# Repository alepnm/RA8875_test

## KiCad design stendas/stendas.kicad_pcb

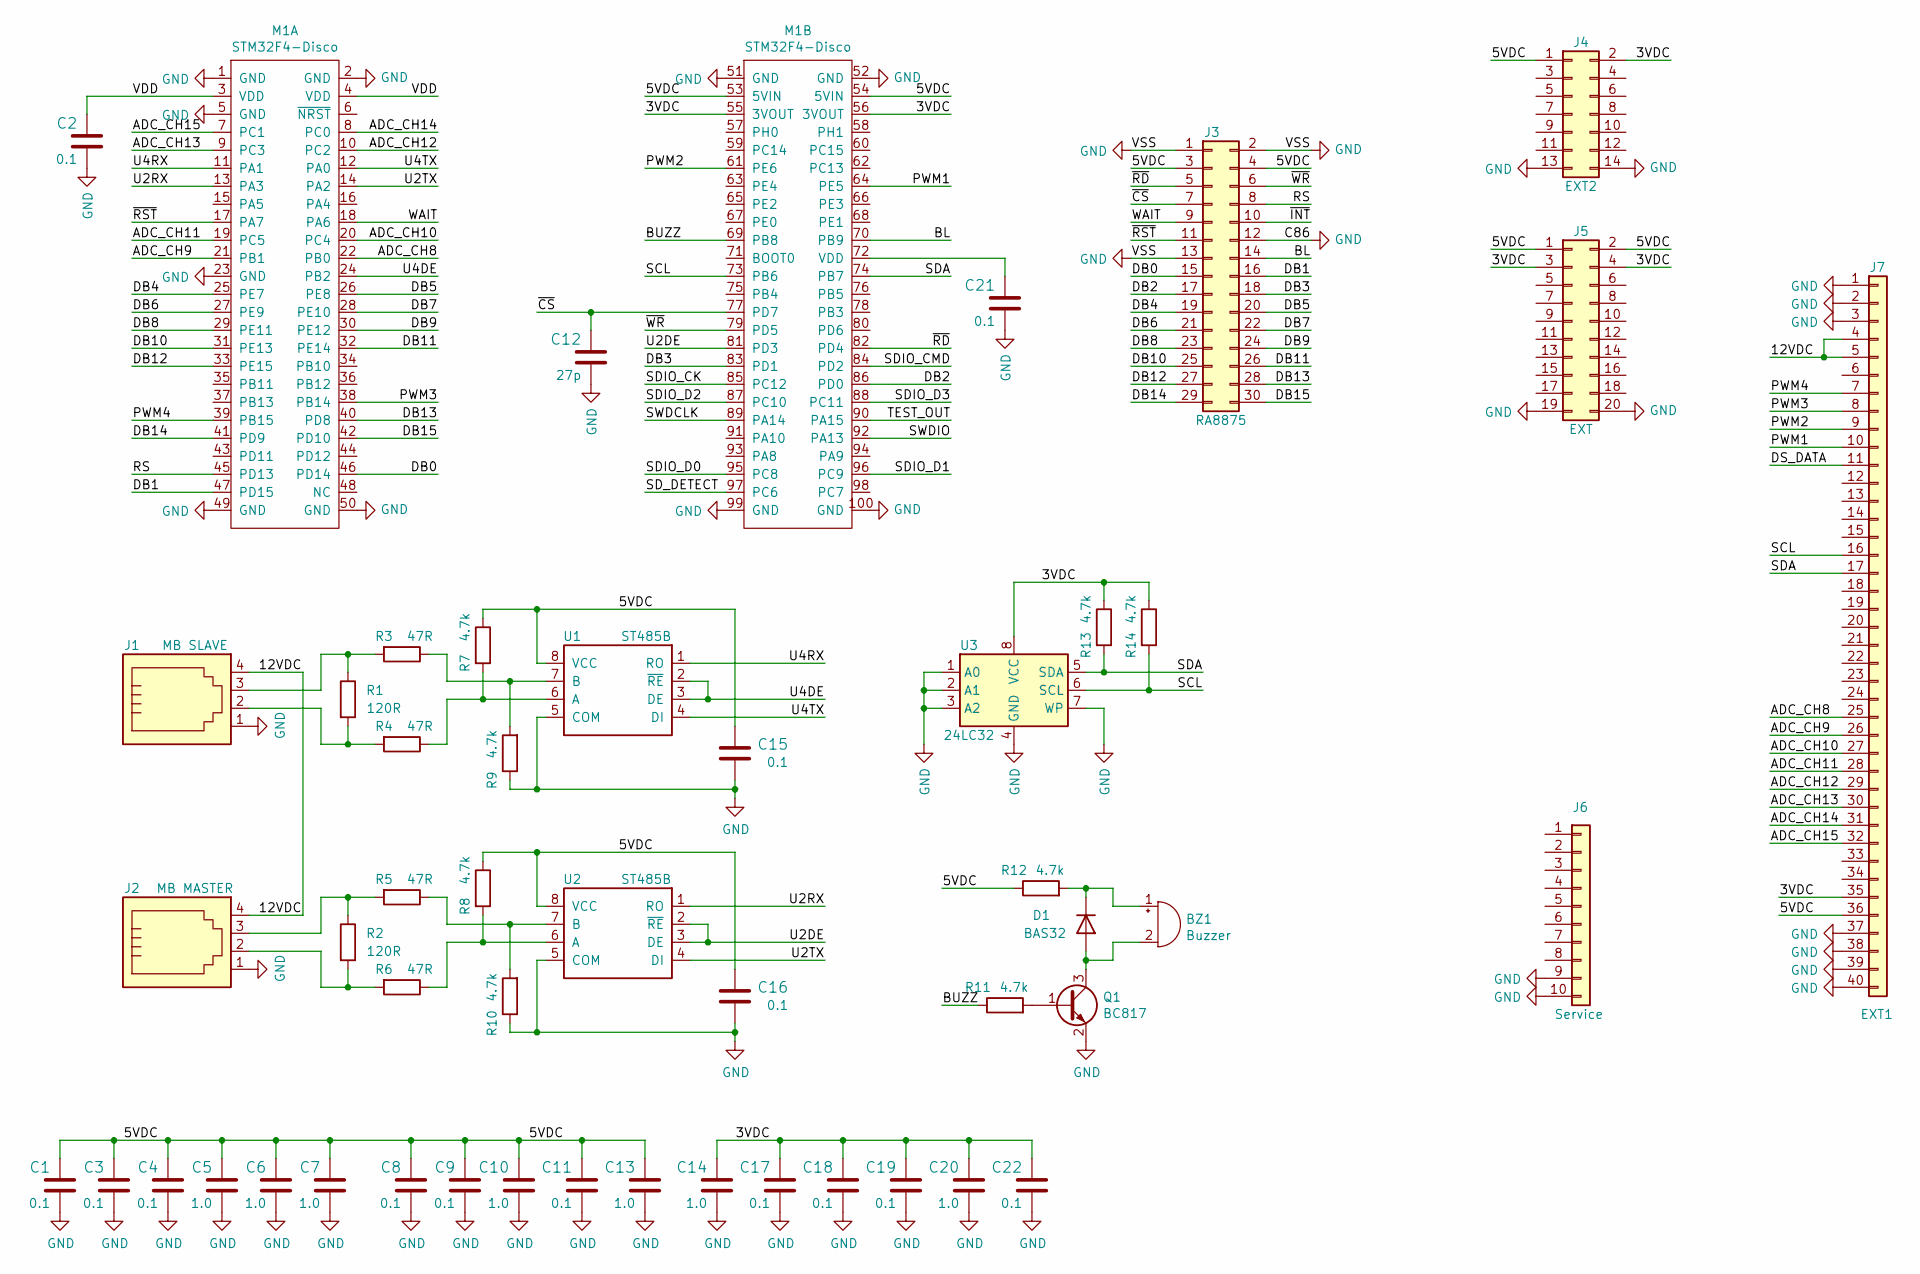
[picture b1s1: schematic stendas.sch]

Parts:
BZ1: Buzzer; MagneticBuzzer_Kobitone_254-EMB84Q-RO
C1, C2, C3, C4, C8, C9, C11, C15, C16, C17, C18, C19, C21, C22: 0.1; C_0805_2012Metric
C5, C6, C7, C10, C13, C14, C20: 1.0; C_1206_3216Metric
C12: 27p
D1: BAS32; D_MiniMELF
J1: MB SLAVE; RJ11_4P_Vertical_DIP
J2: MB MASTER; RJ11_4P_Vertical_DIP
J3: RA8875; PinHeader_2x15_P2.54mm_Vertical
J4: EXT2; IDC-Header_2x07_P2.54mm_Vertical
J5: EXT; IDC-Header_2x10_P2.54mm_Vertical
J6: Service; PinHeader_1x10_P2.54mm_Vertical
J7: EXT1; PinHeader_1x40_P2.54mm_Vertical
M1: STM32F4-Disco; STM32F4_Disco
Q1: BC817; SOT-23
R1, R2: 120R; R_1206_3216Metric
R3, R4, R5, R6: 47R; R_0805_2012Metric
R7, R8, R9, R10, R11, R12, R13, R14: 4.7k; R_0805_2012Metric
U1, U2: ST485B; SOIC-8_3.9x4.9mm_P1.27mm
U3: 24LC32; SOIC-8_3.9x4.9mm_P1.27mm

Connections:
/3VDC: C14.2, C17.2, C18.2, C19.2, C20.2, C22.2, J4.2, J5.3, J5.4, J7.35, M1.55 (3VOUT), M1.56 (3VOUT), R13.1, R14.1, U3.8 (VCC)
/5VDC: C1.2, C3.2, C4.2, C5.2, C6.2, C7.2, C8.2, C9.2, C10.2, C11.2, C13.2, C15.2, C16.2, J3.3, J3.4, J4.1, J5.1, J5.2, J7.36, M1.53 (5VIN), M1.54 (5VIN), R7.1, R8.1, R12.1, U1.8 (VCC), U2.8 (VCC); also elsewhere on the board
/12VDC: J1.4, J2.4, J7.4, J7.5
/ADC_CH8: J7.25, M1.22 (PB0)
/ADC_CH9: J7.26, M1.21 (PB1)
/ADC_CH10: J7.27, M1.20 (PC4)
/ADC_CH11: J7.28, M1.19 (PC5)
/ADC_CH12: J7.29, M1.10 (PC2)
/ADC_CH13: J7.30, M1.9 (PC3)
/ADC_CH14: J7.31, M1.8 (PC0)
/ADC_CH15: J7.32, M1.7 (PC1)
/BL: J3.14, M1.70 (PB9)
/BUZZ: M1.69 (PB8), R11.1; also elsewhere on the board
/DB0: J3.15, M1.46 (PD14)
/DB1: J3.16, M1.47 (PD15)
/DB2: J3.17, M1.86 (PD0)
/DB3: J3.18, M1.83 (PD1)
/DB4: J3.19, M1.25 (PE7)
/DB5: J3.20, M1.26 (PE8)
/DB6: J3.21, M1.27 (PE9)
/DB7: J3.22, M1.28 (PE10)
/DB8: J3.23, M1.29 (PE11)
/DB9: J3.24, M1.30 (PE12)
/DB10: J3.25, M1.31 (PE13)
/DB11: J3.26, M1.32 (PE14)
/DB12: J3.27, M1.33 (PE15)
/DB13: J3.28, M1.40 (PD8)
/DB14: J3.29, M1.41 (PD9)
/DB15: J3.30, M1.42 (PD10)
/DS_DATA: J7.11
/PWM1: J7.10, M1.64 (PE5)
/PWM2: J7.9, M1.61 (PE6)
/PWM3: J7.8, M1.38 (PB14)
/PWM4: J7.7, M1.39 (PB15)
/RS: J3.8, M1.45 (PD13)
/SCL: J7.16, M1.73 (PB6), R14.2, U3.6 (SCL)
/SDA: J7.17, M1.74 (PB7), R13.2, U3.5 (SDA)
/SDIO_CK: M1.85 (PC12)
/SDIO_CMD: M1.84 (PD2)
/SDIO_D0: M1.95 (PC8)
/SDIO_D1: M1.96 (PC9)
/SDIO_D2: M1.87 (PC10)
/SDIO_D3: M1.88 (PC11)
/SD_DETECT: M1.97 (PC6)
/SWDCLK: M1.89 (PA14)
/SWDIO: M1.92 (PA13)
/TEST_OUT: M1.90 (PA15)
/U2DE: M1.81 (PD3), U2.2 (~RE), U2.3 (DE)
/U2RX: M1.13 (PA3), U2.1 (RO)
/U2TX: M1.14 (PA2), U2.4 (DI)
/U4DE: M1.24 (PB2), U1.2 (~RE), U1.3 (DE); also elsewhere on the board
/U4RX: M1.11 (PA1), U1.1 (RO); also elsewhere on the board
/U4TX: M1.12 (PA0), U1.4 (DI); also elsewhere on the board
/VDD: C2.2, M1.3 (VDD), M1.4 (VDD)
/WAIT: J3.9, M1.18 (PA6)
/~CS: C12.2, J3.7, M1.77 (PD7)
/~INT: J3.10
/~RD: J3.5, M1.82 (PD4)
/~RST: J3.11, M1.17 (PA7)
/~WR: J3.6, M1.79 (PD5)
GND: C1.1, C2.1, C3.1, C4.1, C5.1, C6.1, C7.1, C8.1, C9.1, C10.1, C11.1, C12.1, C13.1, C14.1, C15.1, C16.1, C17.1, C18.1, C19.1, C20.1, C21.1, C22.1, J1.1, J2.1, J3.1, J3.2, J3.12, J3.13, J4.13, J4.14, J5.19, J5.20, J6.9, J6.10, J7.1, J7.2, J7.3, J7.37, J7.38, J7.39, J7.40, M1.1 (GND), M1.2 (GND), M1.5 (GND), M1.23 (GND), M1.49 (GND), M1.50 (GND), M1.51 (GND), M1.52 (GND), M1.99 (GND), M1.100 (GND), Q1.2 (E), R9.1, R10.1, U1.5 (COM), U2.5 (COM), U3.1 (A0), U3.2 (A1), U3.3 (A2), U3.4 (GND), U3.7 (WP)
unnamed: BZ1.1 (-), D1.1 (K), R12.2
unnamed: BZ1.2 (+), D1.2 (A), Q1.3 (C)
unnamed: C21.2, M1.72 (VDD)
unnamed: J1.2, R1.2, R4.2
unnamed: J1.3, R1.1, R3.2
unnamed: J2.2, R2.2, R6.2
unnamed: J2.3, R2.1, R5.2
unnamed: Q1.1 (B), R11.2
unnamed: R3.1, R9.2, U1.7 (B)
unnamed: R4.1, R7.2, U1.6 (A)
unnamed: R6.1, R8.2, U2.6 (A)
unnamed: R5.1, R10.2, U2.7 (B)

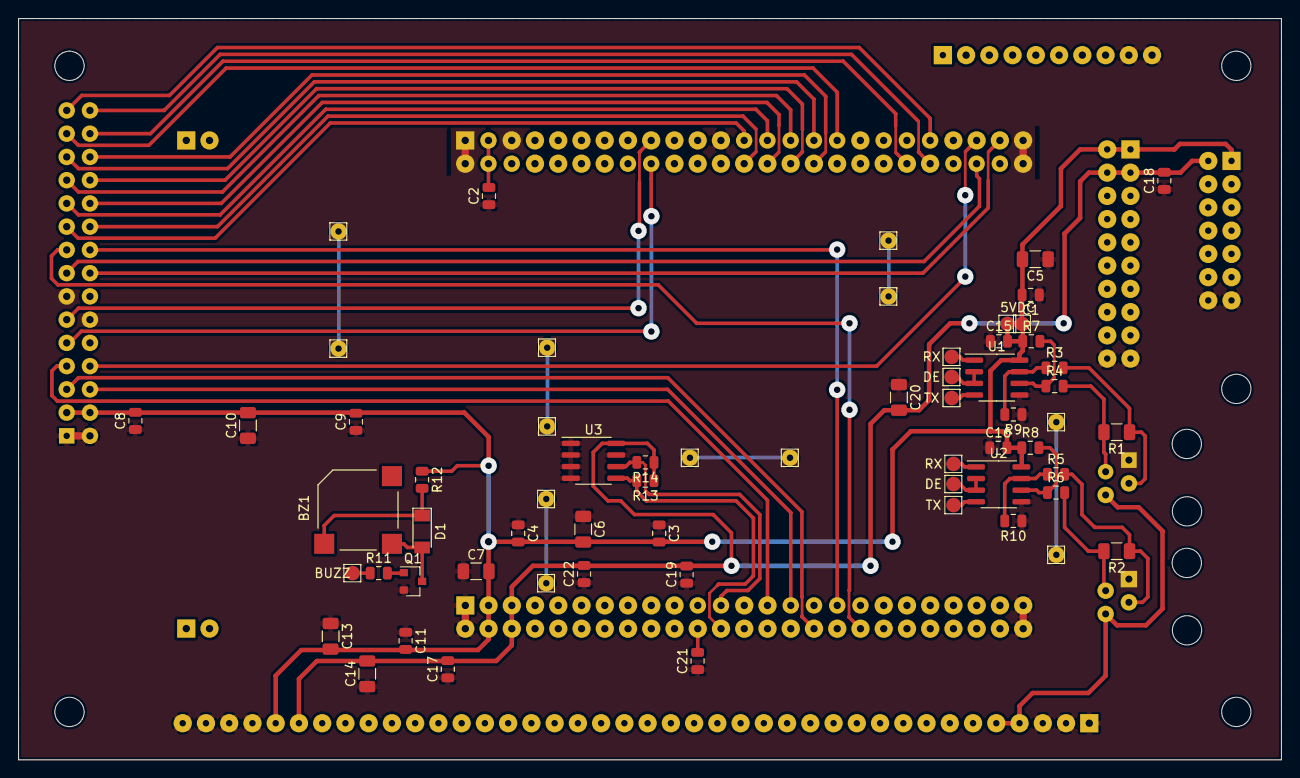
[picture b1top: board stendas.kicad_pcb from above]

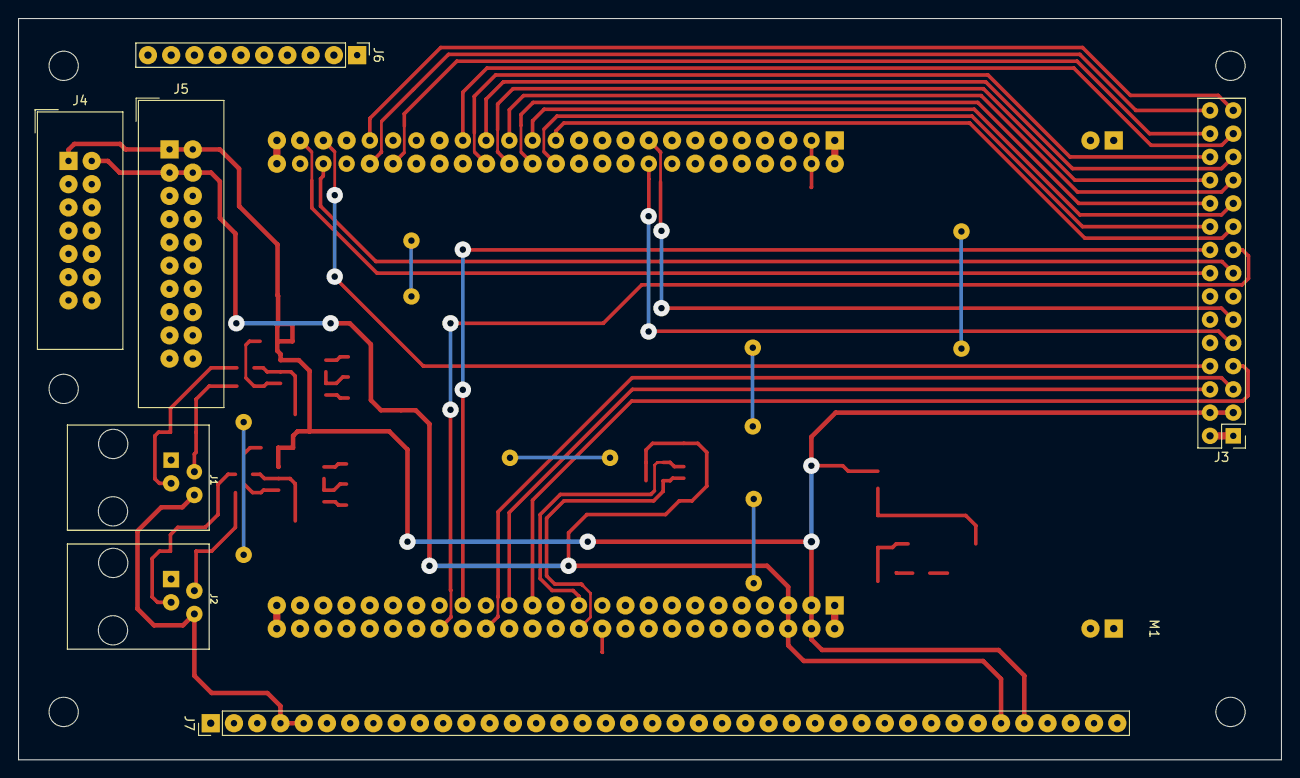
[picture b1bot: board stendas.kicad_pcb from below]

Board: 2 copper layers, 138.0 x 81.0 mm, 57 parts (8 on the bottom side), 61 nets.

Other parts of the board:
5VDC: Pin_D0.7mm_L6.5mm_W1.8mm_FlatFork
BUZZ: Pin_D0.7mm_L6.5mm_W1.8mm_FlatFork
DE: Pin_D0.7mm_L6.5mm_W1.8mm_FlatFork
DE#2: Pin_D0.7mm_L6.5mm_W1.8mm_FlatFork
RX: Pin_D0.7mm_L6.5mm_W1.8mm_FlatFork
RX#2: Pin_D0.7mm_L6.5mm_W1.8mm_FlatFork
TX: Pin_D0.7mm_L6.5mm_W1.8mm_FlatFork
TX#2: Pin_D0.7mm_L6.5mm_W1.8mm_FlatFork

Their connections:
/5VDC: 5VDC.1; also elsewhere on the board
/BUZZ: BUZZ.1; also elsewhere on the board
/U4DE: DE#2.1; also elsewhere on the board
/U4RX: RX#2.1; also elsewhere on the board
/U4TX: TX#2.1; also elsewhere on the board

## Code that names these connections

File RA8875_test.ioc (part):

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Mcu.Name=STM32F407V(E-G)Tx
Mcu.Package=LQFP100
Mcu.UserName=STM32F407VGTx
PA0-WKUP.Mode=Asynchronous
PA0-WKUP.Signal=UART4_TX
PA1.Mode=Asynchronous
PA1.Signal=UART4_RX
PA13.Mode=Trace_Asynchronous_SW
PA13.Signal=SYS_JTMS-SWDIO
PA14.Mode=Trace_Asynchronous_SW
PA14.Signal=SYS_JTCK-SWCLK
PA15.GPIOParameters=GPIO_Label
PA15.GPIO_Label=TEST_OUT
PA15.Signal=GPIO_Output
PA2.Mode=Asynchronous
PA2.Signal=USART2_TX
PA3.Mode=Asynchronous
PA3.Signal=USART2_RX
PA4.Signal=COMP_DAC1_group
PA5.Signal=COMP_DAC2_group
PA6.GPIOParameters=GPIO_Label
PA6.GPIO_Label=LCD_WAIT
PA6.Signal=GPIO_Input
PA7.GPIOParameters=PinState,GPIO_Label
PA7.GPIO_Label=LCD_RST
PA7.PinState=GPIO_PIN_SET
PA7.Signal=GPIO_Output
PA9.GPIOParameters=GPIO_Label
PA9.GPIO_Label=LD7
PA9.Signal=GPIO_Output
PB0.Signal=ADCx_IN8
PB1.Signal=ADCx_IN9
PB14.GPIOParameters=GPIO_Label
PB14.GPIO_Label=PWM3
PB14.Signal=S_TIM12_CH1
PB15.GPIOParameters=GPIO_Label
PB15.GPIO_Label=PWM4
PB15.Signal=S_TIM12_CH2
PB2.GPIOParameters=PinState,GPIO_Label
PB2.GPIO_Label=U4DE
PB2.PinState=GPIO_PIN_RESET
PB2.Signal=GPIO_Output
PB3.Mode=Trace_Asynchronous_SW
PB3.Signal=SYS_JTDO-SWO
PB6.GPIOParameters=GPIO_Speed
PB6.GPIO_Speed=GPIO_SPEED_FREQ_HIGH
PB6.Mode=I2C
PB6.Signal=I2C1_SCL
PB7.GPIOParameters=GPIO_Speed
PB7.GPIO_Speed=GPIO_SPEED_FREQ_HIGH
PB7.Mode=I2C
PB7.Signal=I2C1_SDA
PB8.Signal=S_TIM10_CH1
PB9.GPIOParameters=GPIO_Label
PB9.GPIO_Label=LCD_BACKLIGHT
PB9.Signal=S_TIM11_CH1
PC0.Signal=ADCx_IN10
PC1.Signal=ADCx_IN11
PC10.Mode=SD_4_bits_Wide_bus
PC10.Signal=SDIO_D2
PC11.Mode=SD_4_bits_Wide_bus
PC11.Signal=SDIO_D3
PC12.Mode=SD_4_bits_Wide_bus
PC12.Signal=SDIO_CK
PC13-ANTI_TAMP.GPIOParameters=GPIO_PuPd,GPIO_Label
PC13-ANTI_TAMP.GPIO_Label=DS_DATA
PC13-ANTI_TAMP.GPIO_PuPd=GPIO_PULLUP
PC13-ANTI_TAMP.Signal=GPIO_Input
PC14-OSC32_IN.Mode=LSE-External-Oscillator
PC14-OSC32_IN.Signal=RCC_OSC32_IN
PC15-OSC32_OUT.Mode=LSE-External-Oscillator
PC15-OSC32_OUT.Signal=RCC_OSC32_OUT
PC2.Signal=ADCx_IN12
PC3.Signal=ADCx_IN13
PC4.Signal=ADCx_IN14
PC5.Signal=ADCx_IN15
PC6.GPIOParameters=GPIO_PuPd,GPIO_Label
PC6.GPIO_Label=SD_DETECT
PC6.GPIO_PuPd=GPIO_PULLUP
PC6.Signal=GPIO_Input
PC8.Mode=SD_4_bits_Wide_bus
PC8.Signal=SDIO_D0
PC9.Mode=SD_4_bits_Wide_bus
PC9.Signal=SDIO_D1
PD0.Mode=16b-d1
PD0.Signal=FSMC_D2
PD1.Mode=16b-d1
PD1.Signal=FSMC_D3
PD10.Mode=16b-d1
PD10.Signal=FSMC_D15
PD13.Mode=A18_1
PD13.Signal=FSMC_A18
PD14.Mode=16b-d1
PD14.Signal=FSMC_D0
PD15.Mode=16b-d1
PD15.Signal=FSMC_D1
PD2.Mode=SD_4_bits_Wide_bus
PD2.Signal=SDIO_CMD
PD3.GPIOParameters=GPIO_Label
PD3.GPIO_Label=U2DE
PD3.Signal=GPIO_Output
PD4.Mode=Lcd1
PD4.Signal=FSMC_NOE
PD5.Mode=Lcd1
PD5.Signal=FSMC_NWE
PD7.Mode=NorPsramChipSelect1_1
PD7.Signal=FSMC_NE1
PD8.Mode=16b-d1
PD8.Signal=FSMC_D13
PD9.Mode=16b-d1
PD9.Signal=FSMC_D14
PE0.GPIOParameters=GPIO_PuPd,GPIO_Label,GPIO_ModeDefaultEXTI
PE0.GPIO_Label=RA8875_INT
PE0.GPIO_ModeDefaultEXTI=GPIO_MODE_IT_FALLING
PE0.GPIO_PuPd=GPIO_PULLUP
PE0.Signal=GPXTI0
PE10.Mode=16b-d1
PE10.Signal=FSMC_D7
PE11.Mode=16b-d1
PE11.Signal=FSMC_D8
PE12.Mode=16b-d1
PE12.Signal=FSMC_D9
PE13.Mode=16b-d1
PE13.Signal=FSMC_D10
PE14.Mode=16b-d1
PE14.Signal=FSMC_D11
PE15.Mode=16b-d1
PE15.Signal=FSMC_D12
PE5.GPIOParameters=GPIO_Label
PE5.GPIO_Label=PWM1
PE5.Signal=S_TIM9_CH1
PE6.GPIOParameters=GPIO_Label
PE6.GPIO_Label=PWM2
PE6.Signal=S_TIM9_CH2
PE7.Mode=16b-d1
PE7.Signal=FSMC_D4
PE8.Mode=16b-d1
PE8.Signal=FSMC_D5
PE9.Mode=16b-d1
PE9.Signal=FSMC_D6
PH0-OSC_IN.Mode=HSE-External-Oscillator
PH0-OSC_IN.Signal=RCC_OSC_IN
PH1-OSC_OUT.Mode=HSE-External-Oscillator
PH1-OSC_OUT.Signal=RCC_OSC_OUT
RCC.HSE_VALUE=8000000
RCC.SYSCLKFreq_VALUE=168000000
RCC.SYSCLKSource=RCC_SYSCLKSOURCE_PLLCLK
board=nextion_hmi

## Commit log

2020-03-22 inicializavimas
2020-03-24 lcd veikia, cgram ir ext.rom fontai vaikia; touch dar neveikia
2020-03-27 lcd, fsmc, touchpad, internal fontas, fontas is isorines mikroschemos ir fontas is failu veikia;
2020-03-27 emwin inicializavimas
2020-03-28 emwin derinimas
2020-03-28 emwin derinimas: projektas kompiliuojasi, nepakimba, bet dar ir neveikia kaip priklauso. reikia turbut aprasyri tvarkingai emwin ra8875 displejaus draiveri
2020-03-28 nereikalingu failu salinimas
2020-03-28 sutvarkytas bugas, kai emwin neteisingai atvaizdavo uzdazomus regionus (rode tik ju konturus). dabar viskas atvaizduojama tvarkingai
2020-03-30 touch modulio pritaikymas prie emwin, lib failas paimtas is off. bibliotekos
2020-03-30 touch padas veikia pakankamai patikimai
2020-03-31 examples.c - pavyzdziu failas
2020-04-02 prijungta ir sugonfiguruota freertos biblioteka; emwin pritaikytas darbui su freertos - viskas veikia
2020-04-04 inicializacija; gui demo veikia tvarkingai; reikia ziureti kodel tekstas is isorinio zenklu generatoriaus isvedamas su iskraipymais pliko fsmc rezime (turbut kazkas su sios mikroschemos dazniu?); is 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
2020-04-04 temp
2020-04-05 temp; letai veikia ir tik debug konfiguracijoje
2020-04-05 perrasytos pagrindines ra8875 registru ir DDRAM skaitymo-rasymo funkcijos, dabar veikia ir debug ir release konfiguracijose, bet dar netinkamai veikia GUIDEMO RadialMenu (toks ispudis, kad framerate 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
2020-04-05 aprasytas ir veikia WM testinis modulis
2020-04-06 emwin windows manager pilnai veikia
2020-04-06 branch init; prijungta freertos biblioteka, sukonfiguruotas emwin darbui su freertos
2020-04-06 prijungta freemodbus biblioteka
2020-04-08 sukonfiguruota ir paleista freemodbus biblioteka, modbus veikia. paleistas us taimeris - TIM7. Pastebetas Cube bugas, kai pergeneruojant projekta perrasoma defaino HSE_VALUE reiksme i 25000000 faile 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
    Po projekto pergeneravimo reikia butinai pakeisti defaino HSE_VALUE reiksme i 8000000 (naudojamo HSE kvarco daznis) faile stm32f4xx_ll_rcc.h
2020-04-09 prijungta ds18b20 biblioteka; daviklius mato ir skaito
2020-04-10 aktyvuotas adc ir dma, TIM8 pwm formavimui; viskas veikia
2020-04-10 schemos ir pcb projekto paruosimas
2020-04-11 schemos ir pcb paruosimas
2020-04-11 aktyvuotas papildomas hardwaras - taimeris garsui, du analoginiai iejimai, i2c
2020-04-12 pirma plokstes versija
2020-04-12 paketimai po displejaus ir STM32F4-Disco perkelimo i nauja shield'a - naujai pagaminta plokste
2020-04-13 prijungta fatfs biblioteka; padarytas pinu remapas
2020-04-13 paleistas primary port modbusas per rs485
2020-04-13 remapinti pinai - plokste pritaikyta darbui su sd-card
2020-04-18 pakeista projekto failu struktura, pradetas rasyti BTE modulis
2020-05-07 bandymas BTE funkciju
2020-07-18 pasalintas emwin, kodo rasymas
2020-07-22 sutvarkytas darbas su isoriniu spi flash'u; surasyti RA8875 registru ir ju bitu defainai (dar nevisu); dabar viskas veikia - skaitomos duomenys is flash'o ir isvedami i lcd
2020-07-23 ra8875 bibliotekos kodo rasymas
2020-07-24 prijungta emwin bibloiteka
2020-07-26 sutvarkyta touch panel biblioteka, dabar tp veikia tvarkingai
